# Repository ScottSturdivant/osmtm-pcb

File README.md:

# osmtm-pcb
Overnight Sensations MTM Printed Circuit Board Project

The [OS MTM](https://sites.google.com/site/undefinition/overnightsensationmtm) is a nice little speaker setup designed by Paul Carmody.
There are DIY kits available at [DIY Sound Group](http://www.diysoundgroup.com/speaker-kits/overnight-sensation/osmtm-flat-pack.html).  If
you're nervous about assembling the crossover, you may simply take these Gerber files and get them produced from any PCB manufacturer.
The cost is ~$20USD for 5 boards from the cheaper Chinese shops while some (PCBWay) offer $1/board for 10 boards if under 100mm x 100mm.

## Why
While waiting for the OS MTM kits to come back in stock, and hating the idea of an MDF or pegboard based crossover, I figured I'd dust off my EE skills
and take a stab at laying out a PCB, using the [KiCad](http://kicad-pcb.org) program.  This is purely overkill, you do not *need* a PCB, but it sure is nice.  And pretty.  Inside your
speaker cabinet.

## Schematic
To start, I took Paul's original schematic:

And redrew it in KiCad:

## Footprints
The Bill of Materials was cross referenced against the part spec sheets to draw the footprints for the various components.  The inductors
however were slightly made up as I didn't have the inner diameter of the coil.

Mounting holes for standard 3mm pan head wood screws are included, but standoffs are required.

There are holes for zip ties with a max width of 5mm used to hold the inductors in place.

The resulting PCB winds up looking like this:

## PCB Board

Using the excellent 3D models included with KiCad, here's what the board will mostly look like once built and assembled:

Front:

Back:

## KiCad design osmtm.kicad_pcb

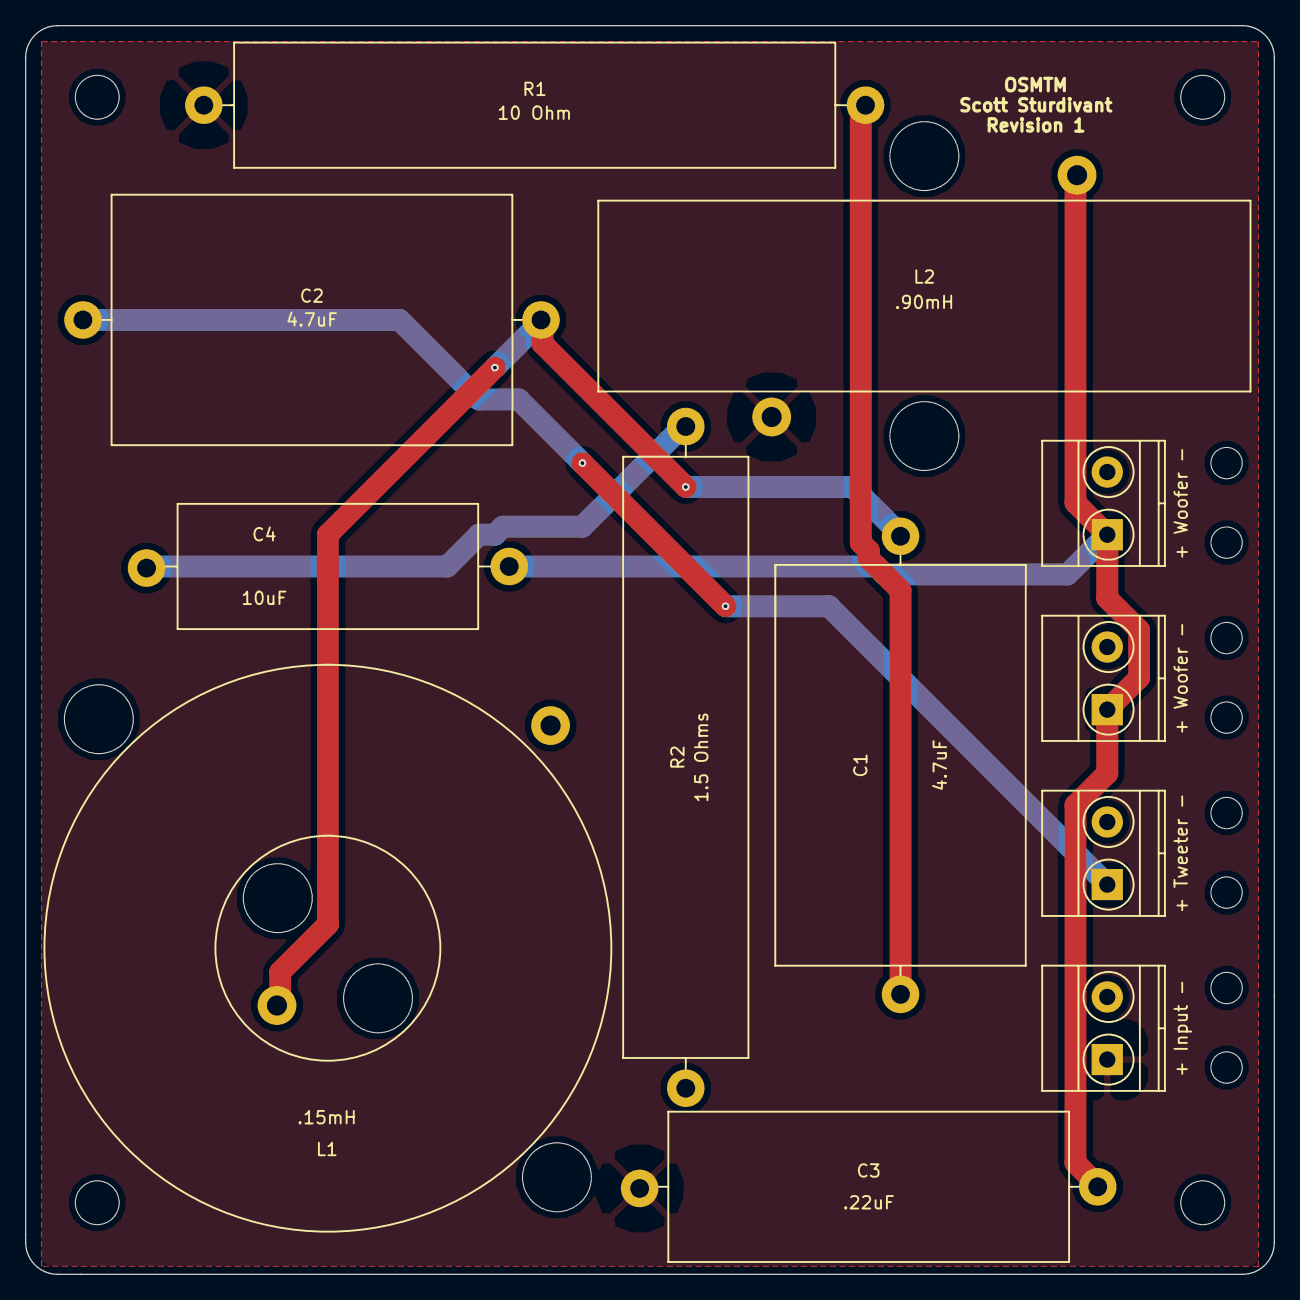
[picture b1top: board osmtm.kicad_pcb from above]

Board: 2 copper layers, 99.7 x 99.7 mm, 12 parts (0 on the bottom side), 7 nets.

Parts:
+ Input -: Screw_Terminal_1x02; TerminalBlock_Pheonix_MKDS1.5-2pol
+ Tweeter -: Speaker; TerminalBlock_Pheonix_MKDS1.5-2pol
+ Woofer -: Speaker; TerminalBlock_Pheonix_MKDS1.5-2pol
+ Woofer -#2: Speaker; TerminalBlock_Pheonix_MKDS1.5-2pol
C1, C2: 4.7uF; Dayton4.7uF
C3: .22uF; Dayton0.22uF
C4: 10uF; Dayton10uFNPE
L1: .15mH; JantzenAudio0.15mhInductor
L2: .90mH; JantzenAudio90mHInductor
R1: 10 Ohm; Dayton10Ohm
R2: 1.5 Ohms; Dayton1.5Ohm

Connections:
BLACK: + Input -.2, + Tweeter -.2, + Woofer -.2, + Woofer -#2.2, L1.2, R2.2
unnamed: C1.1, C2.2, L1.1
unnamed: C1.2, R1.1
unnamed: + Tweeter -.1, C2.1
unnamed: + Woofer -.1, + Woofer -#2.1, C3.1, C4.1, L2.1
unnamed: C4.2, R2.1
RED: + Input -.1, C3.2, L2.2, R1.2

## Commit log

2017-01-10 Initial commit of the OSMTM PCB.
2017-01-10 Fix DIY sound group link in README.
2017-01-11 Use screw terminals, increase trace width.
    The trace width was incorrectly using the results for external lines
    when it should have been using internal. As a result of this (and the
    screw terminal change), the inductor footprints were also modified and
    the amount of zip ties used reduced.
2017-01-11 Update README with new screenshots.
2017-01-11 Update schematic pic in README.
2017-01-12 Adapt board to 100mm x 100mm sizing.
